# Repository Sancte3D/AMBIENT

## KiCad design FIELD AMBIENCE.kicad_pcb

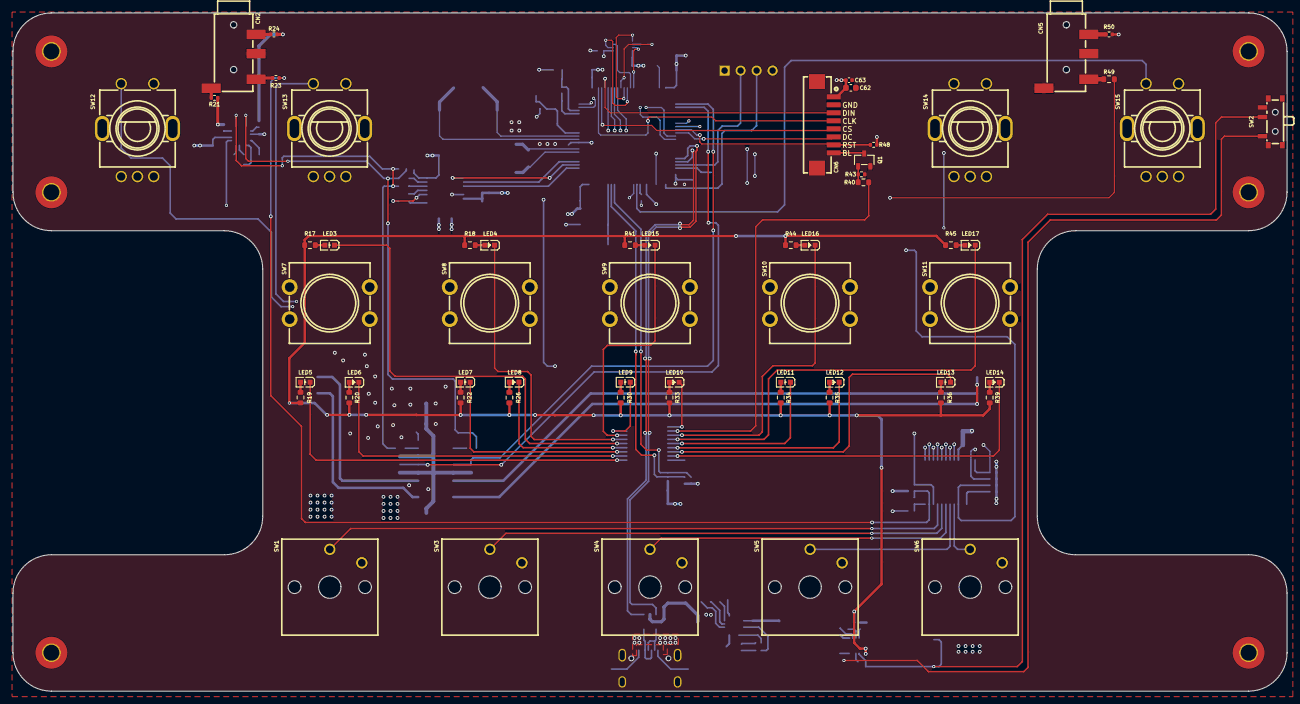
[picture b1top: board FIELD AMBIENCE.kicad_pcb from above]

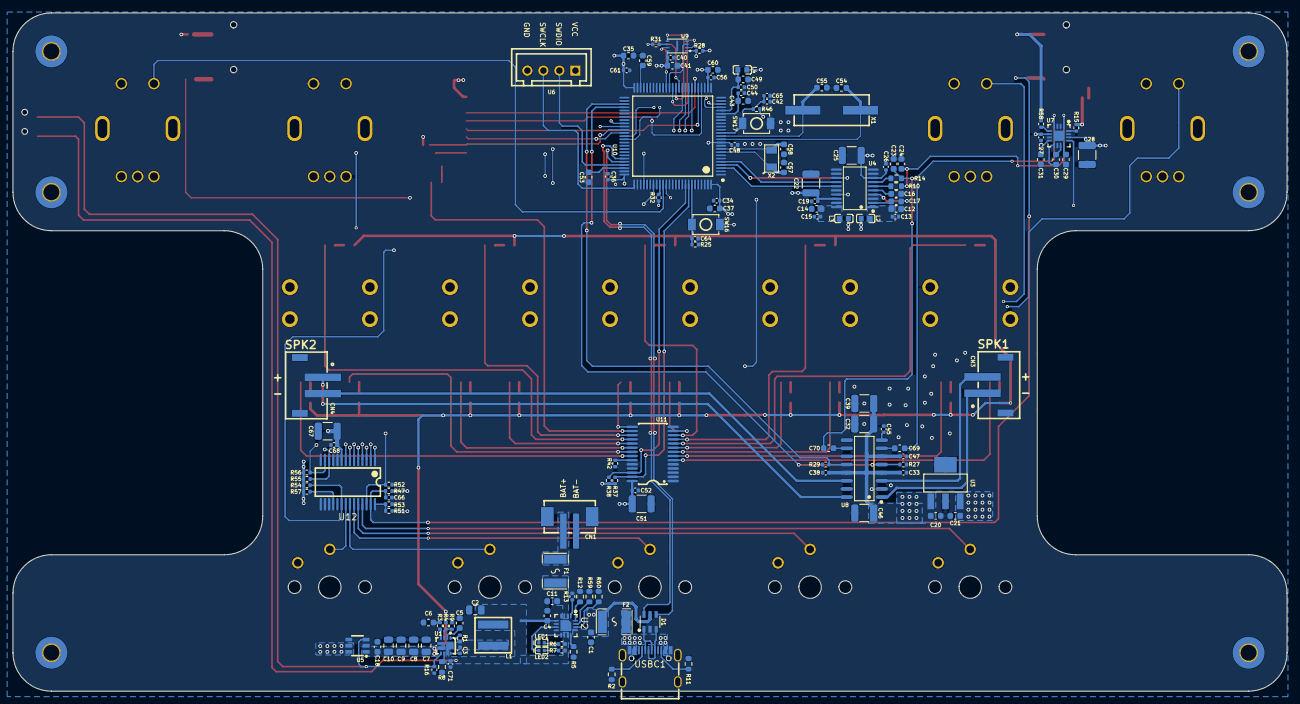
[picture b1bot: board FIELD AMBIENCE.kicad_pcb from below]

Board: 4 copper layers, 198.9 x 105.9 mm, 200 parts (135 on the bottom side), 159 nets.

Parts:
C1, C18, C30, C31, C69, C70: 1uF; C_0603_1608Metric
C2, C7, C8, C9, C10: 22uF; C_0805_2012Metric
C3, C13, C15, C19, C26, C27, C33, C34, C36, C38, C40, C42, C44, C45, C47, C48, C50, C52, C56, C61, C63, C64, C65, C66, C68, C71: 100nF; C_0402_1005Metric
C4, C11, C20, C21, C35, C62: 4.7uF; C_0603_1608Metric
C5, C16, C17, C23, C24, C29, C53, C59: 2.2uF; C_0603_1608Metric
C6: 4.7nF; C_0603_1608Metric
C12, C14, C37, C41, C43, C49, C60: 10uF; C_0603_1608Metric
C22, C25, C28, C32, C39, C46, C51, C67: 10uF; C_1210_3225Metric
C54, C55: 27pF; C_0603_1608Metric
C57, C58: 15pF; C_0603_1608Metric
CN1: B2B-PH-SM4-TBT; CONN-SMD_B2B-PH-SM4-TBT-LF-SN
CN2, CN5: PJ-320D; AUDIO-SMD_PJ-320D-1
CN3, CN4: 2.54-2P LT; CONN-SMD_2.54-2PLT
CN6: HC-1.25-8PWT; CONN-SMD_HC-1.25-8PWT
D1: USBLC6-2SC6; SOT-23-6_L2.9-W1.6-P0.95-LS2.8-BL
F1: 1812P260TF; F1812
F2: 1812L300/16GR; F1812
H2, H3, H4, H5, H6, H7: MountingHole_Pad; MountingHole_2.5mm_Pad_TopBottom
L1: 1.8uH; IND-SMD_L5.5-W5.3_YSPIT0530A
L2, L3: BLM18AG601SN1D; L0603
L4: BLM18PG121SN1D; L0603
LED1, LED2: YLED0402B; LED0402-RD
LED3, LED5, LED7, LED9, LED11, LED13: Yellow; LED0603-R-RD
LED4, LED6, LED8, LED10, LED12, LED14: Green; LED0603-RD
LED15, LED16, LED17: XL-1608UWC-04; LED0603-RD_WHITE
Q1: 2N7002_C916396; SOT-23-3_L2.9-W1.3-P1.90-LS2.4-BR
R1: 301K; R_0402_1005Metric
R2, R11: 5.1K; R_0603_1608Metric
R3: 17.4K; R_0402_1005Metric
R4: 332K; R_0402_1005Metric
R5: 1.1K; R_0603_1608Metric
R6, R7: 1.5K; R_0402_1005Metric
R8: 348K; R_0603_1608Metric
R9: 107K; R_0402_1005Metric
R10, R14: 470R; R_0603_1608Metric
R12: 887R; R_0603_1608Metric
R13, R23, R25, R28, R42, R43, R46, R47, R48, R50, R52, R54, R57: 10K; R_0402_1005Metric
R15, R58: 0R; R_0402_1005Metric
R16, R27, R29, R32, R51: 100K; R_0402_1005Metric
R17, R18, R19, R20, R22, R26, R30, R33, R34, R35, R36, R39, R41, R44, R45: 390R; R_0603_1608Metric
R21, R24, R31: 33R; R_0402_1005Metric
R37, R38, R55, R56: 4.7K; R_0402_1005Metric
R40: 100R; R_0603_1608Metric
R49: 220R; R_0603_1608Metric
R53: 200K; R_0402_1005Metric
R59: 590R; R_0603_1608Metric
R60: 37.4K; R_0603_1608Metric
SW1, SW3, SW4, SW5, SW6: CPG135001D01; KEY-TH_CPG135001D0X
SW2: SSSS811101; SW-SMD_SSSS811101
SW7, SW8, SW9, SW10, SW11: HX B3F-4055-Y; SW-TH_4P-L12.0-W12.0-P5.00-LS12.5_HX-B3F-4055-Y
SW12, SW13, SW14, SW15: EC11E18244AU; SW-TH_EC11XXXXXXXX
SW16, SW17: TS-1088; SW-SMD_L3.9-W3.0-P4.45
U1: TPS61089RNRR; VQFN-HR_L2.5-W2.0-P0.50-TL-EP
U2: BQ24074RGTR; QFN-16_L3.0-W3.0-P0.50-TL-EP1.7
U3: AP7361C-33E-13; SOT-223_L6.5-W3.5-P2.30-LS7.0-BR
U4: PCM5102APWR; TSSOP-20_L6.5-W4.4-P0.65-LS6.4-BL
U5: TPS22918DBVR; SOT-23-6_L2.9-W1.6-P0.95-LS2.8-BR
U6: B4B-XH-A; CONN-TH_B4B-XH-A-BK-LF-SN
U7: TPA6132A2RTER; WQFN-16_L3.0-W3.0-P0.50-TL-EP1.6
U8: PAM8403DR; SOIC-16_L9.9-W3.9-P1.27-LS6.0-BL
U9: APS6404L-3SQR-ZR; USON-8_L3.0-W2.0-P0.50-BL-EP
U10: STM32H743VIT6_C114409; LQFP-100_L14.0-W14.0-P0.50-LS16.0-BL
U11: PCA9685PW,118; TSSOP-28_L9.7-W4.4-P0.65-LS6.4-TL
U12: MCP23017T-E/SS; SSOP-28_L10.2-W5.3-P0.65-LS7.8-BL
USBC1: TYPE-C-31-M-12; USB-C_SMD-TYPE-C-31-M-12_1
X1: ABLS-8.000MHZ-B4-T; CRYSTAL-SMD_L11.4-W4.7-LS12.7
X2: ABS07-32.768KHZ-T; OSC-SMD_2P-L3.2-W1.5

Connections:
3.3V: C19.2, C21.2, C22.1, C25.2, C26.2, C27.2, C28.2, C34.2, C35.2, C36.1, C37.2, C40.2, C41.2, C48.2, C51.2, C52.2, C56.2, C60.2, C61.2, C62.2, C63.2, C67.2, C68.2, CN6.1, L2.1, L3.2, L4.2, R28.1, R37.1, R38.1, R46.1, R47.2, R48.1, R50.2, R54.1, R55.1, R56.1, R57.1, SW16.2, U3.3 (OUT), U4.8 (AVDD), U4.18 (LDOO), U6.1, U7.6 (G0), U7.14 (VDD), U9.8 (VDD), U10.11 (VDD), U10.27 (VDD), U10.50 (VDD), U10.75 (VDD), U10.100 (VDD), U11.28 (VDD), U12.9 (VDD)
+5V: C7.2, C8.2, C9.2, C10.2, C18.2, R4.1, R17.1, R18.1, R19.1, R20.1, R22.1, R26.1, R30.1, R33.1, R34.1, R35.1, R36.1, R39.1, R41.1, R44.1, R45.1, U1.6 (VOUT), U5.1 (VIN)
+5V_SW: C20.2, C32.2, C33.2, C38.2, C39.2, C46.2, C47.2, U3.1 (IN), U5.5 (QOD), U5.6 (VOUT), U8.4 (PVDD), U8.6 (VDD), U8.13 (PVDD)
+OUT_L: CN3.1, U8.1 (+OUT_L)
+OUT_R: CN4.1, U8.16 (+OUT_R)
-OUT_L: CN3.2, U8.3 (-OUT_L)
-OUT_R: CN4.2, U8.14 (-OUT_R)
BCK: U4.13 (BCK), U10.4 (PE5)
BOOT: C64.2, R25.2, SW16.1, U10.94 (BOOT0)
Backlight: CN6.8, Q1.3 (D)
CE: R28.2, U9.1 (/CE), U10.79 (PC11)
DIN: U4.14 (DIN), U10.5 (PE6)
DR+: D1.3 (I/O2), USBC1.A6 (DP1), USBC1.B6 (DP2)
DR-: D1.1 (I/O1), USBC1.A7 (DN1), USBC1.B7 (DN2)
Detect: C66.2, R23.1, R47.1, U12.27 (GPA6)
EXTI4: SW15.D, U10.85 (PD4)
FB: R4.2, R9.1, U1.3 (FB)
GND: C1.1, C2.1, C4.1, C5.1, C6.1, C7.1, C8.1, C9.1, C10.1, C11.2, C12.1, C13.1, C14.1, C15.1, C16.1, C18.1, C19.1, C20.1, C21.1, C22.2, C23.2, C24.2, C25.1, C26.1, C27.1, C28.1, C29.2, C31.1, C32.1, C33.1, C34.1, C35.1, C36.2, C37.1, C38.1, C39.1, C40.1, C41.1, C42.1, C43.1, C44.1, C45.1, C46.1, C47.1, C48.1, C49.1, C50.1, C51.1, C52.1, C53.2, C54.1, C55.1, C56.1, C57.1, C58.1, C59.2, C60.1, C61.1, C62.1, C63.1, C64.1, C65.1, C66.1, C67.1, C68.1, C71.2, CN1.2, CN2.3, CN5.1, CN6.2, D1.2 (GND), Q1.2 (S), R2.1, R5.1, R8.1, R9.2, R11.1, R12.1, R13.1, R16.1, R25.1, R27.1, R29.1, R42.2, R43.2, R52.2, R53.1, R59.1, R60.1, SW1.2, SW3.2, SW4.2, SW5.2, SW6.2, SW7.2, SW8.2, SW9.2, SW10.2, SW11.2, SW12.C, SW12.E, SW13.C, SW13.E, SW14.C, SW14.E, SW15.C, SW15.E, SW17.2, U1.5 (GND), U2.4 (CE#), U2.6 (EN1), U2.8 (VSS), U2.17 (EP), U3.2 (GND), U3.4 (GND), U4.3 (CPGND), U4.9 (AGND), U4.10 (DEMP), U4.11 (FLT), U4.12 (SCK), U4.16 (FMT), U4.19 (DGND), U5.2 (GND), U6.4, U7.2 (INL+), U7.3 (INR+), U7.7 (G1), U7.10 (PGND), U7.15 (SGND), U7.17 (EP), U8.2 (PGND), U8.11 (GND), U8.15 (PGND), U9.4 (VSS), U10.10 (VSS), U10.19 (VSSA), U10.26 (VSS), U10.49 (VSS), U10.74 (VSS), U10.99 (VSS), U11.1 (A0), U11.2 (A1), U11.3 (A2), U11.4 (A3), U11.5 (A4), U11.14 (VSS), U11.24 (A5), U12.10 (VSS), U12.15 (A0), U12.16 (A1), U12.17 (A2), USBC1.1 (EH), USBC1.2 (EH), USBC1.3 (EH), USBC1.4 (EH), USBC1.A1B12 (GND), USBC1.B1A12 (GND)
GPA0: SW6.1, U12.21 (GPA0)
GPA1: SW5.1, U12.22 (GPA1)
GPA2: SW4.1, U12.23 (GPA2)
GPA3: SW3.1, U12.24 (GPA3)
GPA5: SW1.1, U12.25 (GPA4)
GPA7: R51.1, R53.2, U12.28 (GPA7)
GPB0: SW7.3, U12.1 (GPB0)
GPB1: SW8.3, U12.2 (GPB1)
GPB2: SW9.3, U12.3 (GPB2)
GPB3: SW10.3, U12.4 (GPB3)
GPB4: SW11.3, U12.5 (GPB4)
GPB5: SW12.D, U12.6 (GPB5)
GPB6: SW13.D, U12.7 (GPB6)
GPB7: SW14.D, U12.8 (GPB7)
Interrupt: R54.2, U10.82 (PD1), U12.20 (INTA)
LCD CS: CN6.5, U10.30 (PA6)
LCD DC: CN6.6, U10.62 (PD15)
LCD RST: CN6.7, R48.2, U10.61 (PD14)
LCD SCK: CN6.4, U10.29 (PA5)
LD0: LED5.2 (K), U11.6 (LED0)
LD1: LED6.1 (K), U11.7 (LED1)
LD2: LED7.2 (K), U11.8 (LED2)
LD3: LED8.1 (K), U11.9 (LED3)
LD4: LED3.2 (K), U11.10 (LED4)
LD5: LED17.1 (K), U11.18 (LED11)
LD6: LED15.1 (K), U11.12 (LED6)
LD7: LED16.1 (K), U11.17 (LED10)
LD8: LED10.1 (K), U11.15 (LED8)
LD9: LED9.2 (K), U11.13 (LED7)
LD10: LED4.1 (K), U11.11 (LED5)
LD11: LED13.2 (K), U11.21 (LED14)
LD12: LED12.1 (K), U11.20 (LED13)
LD13: LED11.2 (K), U11.19 (LED12)
LD14: R40.1, U11.16 (LED9)
LD15: LED14.1 (K), U11.22 (LED15)
LRCK: U4.15 (LRCK), U10.3 (PE4)
MOSI: CN6.3, U10.31 (PA7)
MUTE: R27.2, U8.5 (MUTE), U10.54 (PB15)
NRST: C42.2, C65.2, R46.2, SW17.1, U10.14 (NRST)
unnamed: C6.2, R3.1
unnamed: C53.1, U10.73 (VCAP)
unnamed: C59.1, U10.48 (VCAP)
unnamed: CN1.1, F1.2
unnamed: CN2.1, R21.1
unnamed: CN2.2, R24.1
unnamed: CN2.4, R23.2
unnamed: CN5.2, R50.1
unnamed: CN5.4, R49.1
unnamed: LED1.2 (A), R6.1
unnamed: LED1.1 (K), U2.9 (CHG#)
unnamed: LED2.2 (A), R7.1
unnamed: LED2.1 (K), U2.7 (PGOOD#)
unnamed: LED3.1 (A), R17.2
unnamed: LED4.2 (A), R18.2
unnamed: LED5.1 (A), R19.2
unnamed: LED6.2 (A), R20.2
unnamed: LED7.1 (A), R22.2
unnamed: LED8.2 (A), R26.2
unnamed: LED9.1 (A), R30.2
unnamed: LED10.2 (A), R33.2
unnamed: LED11.1 (A), R34.2
unnamed: LED12.2 (A), R35.2
unnamed: LED13.1 (A), R36.2
unnamed: LED14.2 (A), R39.2
unnamed: LED15.2 (A), R41.2
unnamed: LED16.2 (A), R44.2
unnamed: LED17.2 (A), R45.2
unnamed: Q1.1 (G), R40.2, R43.1
unnamed: C3.1, U1.10 (BOOT)
unnamed: R3.2, U1.4 (COMP)
unnamed: R1.2, U1.1 (FSW)
unnamed: R8.2, U1.8 (ILIM)
unnamed: C3.2, L1.2, R1.1, U1.11 (SW)
unnamed: C5.2, U1.2 (VCC)
unnamed: R5.2, U2.12 (ILIM)
unnamed: R12.2, U2.16 (ISET)
unnamed: R59.2, U2.15 (ITERM)
unnamed: R60.2, U2.14 (TMR)
unnamed: R13.2, U2.1 (TS)
unnamed: C17.2, U4.4 (CAPM)
unnamed: C17.1, U4.2 (CAPP)
unnamed: C12.2, C13.2, L2.2, U4.1 (CPVDD)
unnamed: C14.2, C15.2, L3.1, U4.20 (DVDD)
unnamed: R10.2, U4.6 (OUTL)
unnamed: R14.2, U4.7 (OUTR)
unnamed: C16.2, U4.5 (VNEG)
unnamed: C30.1, U7.9 (CPN)
unnamed: C30.2, U7.11 (CPP)
unnamed: C29.1, U7.12 (HPVDD)
unnamed: C31.2, U7.8 (HPVSS)
unnamed: R15.1, U7.16 (OUTL)
unnamed: R58.2, U7.5 (OUTR)
unnamed: C69.1, U8.7 (INL)
unnamed: C70.1, U8.10 (INR)
unnamed: C45.2, U8.8 (VREF)
unnamed: R31.1, U9.6 (SCLK)
unnamed: R32.1, U10.84 (PD3)
unnamed: C49.2, C50.2, L4.1, U10.21 (VDDA)
unnamed: R42.1, U11.23 (OE#)
unnamed: R57.2, U12.18 (RESET#)
unnamed: R2.2, USBC1.A5 (CC1)
unnamed: R11.2, USBC1.B5 (CC2)
OSC32_IN: C57.2, U10.8 (PC14-OSC32_IN), X2.1 (OSC1)
OSC32_OUT: C58.2, U10.9 (PC15-OSC32_OUT), X2.2 (OSC2)
OSC_IN: C54.2, U10.12 (PH0-OSC_IN), X1.1 (OSC1)
OSC_OUT: C55.2, U10.13 (PH1-OSC_OUT), X1.2 (OSC2)
OUT DR+: D1.4 (I/O2), U10.71 (PA12)
OUT DR-: D1.6 (I/O1), U10.70 (PA11)
PA0: SW12.A, U10.22 (PA0)
PA1: SW12.B, U10.23 (PA1)
PB0: SW15.B, U10.35 (PB1)
PB1: SW15.A, U10.34 (PB0)
PC4: SW14.A, U10.32 (PC4)
PC5: SW14.B, U10.33 (PC5)
PC6: SW13.A, U10.64 (PC7)
PC7: SW13.B, U10.63 (PC6)
PWR_ON: R16.2, SW2.2, U1.7 (EN), U5.3 (ON)
R_LO_L: R15.2, R21.2
R_LO_R: R24.2, R58.1
R_VOL_L: C24.1, C69.2, R10.1, U7.1 (INL-)
R_VOL_R: C23.1, C70.2, R14.1, U7.4 (INR-)
SCL MCP: R55.2, U10.59 (PD12), U12.12 (SCK)
SCL PCA: R38.2, U10.92 (PB6), U11.26 (SCL)
SCLK: R31.2, U10.36 (PB2)
SDA MCP: R56.2, U10.60 (PD13), U12.13 (SDA)
SDA PCA: R37.2, U10.93 (PB7), U11.27 (SDA)
SHDN: R29.2, U8.12 (SHND), U10.53 (PB14)
SIO0: U9.5 (SI/SIO), U10.37 (PE7)
SIO1: U9.2 (SO/SIO), U10.38 (PE8)
SIO2: U9.3 (SIO), U10.39 (PE9)
SIO3: U9.7 (SIO), U10.40 (PE10)
SWCLKS: U6.3, U10.76 (PA14)
SWDIOS: U6.2, U10.72 (PA13)
TPA6132-EN: R32.2, U7.13 (EN)
USART2_TX: R49.2, U10.86 (PD5)
VBUS: C1.2, D1.5 (VBUS), F2.1, R51.2, U2.13 (IN)
VBUS0: F2.2, USBC1.A4B9 (VBUS), USBC1.B4A9 (VBUS)
VREF+: C43.2, C44.2, U10.20 (VREF+)
VSYS: C2.2, C4.2, C71.1, L1.1, R6.2, R7.2, SW2.1, U1.9 (VIN), U2.5 (EN2), U2.10 (OUT), U2.11 (OUT)
XSMT: R52.1, U4.17 (XSMT), U12.26 (GPA5)
battery: C11.1, F1.1, U2.2 (BAT), U2.3 (BAT)

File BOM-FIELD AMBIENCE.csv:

Comment,Designator,Footprint,LCSC,Quantity
0R,"R15,R58",R_0402_1005Metric,C226739,2
1.1K,R5,R_0603_1608Metric,C22764,1
1.5K,"R6,R7",R_0402_1005Metric,C25867,2
1.8uH,L1,IND-SMD_L5.5-W5.3_YSPIT0530A,C18199436,1
100K,"R16,R27,R29,R32,R51",R_0402_1005Metric,C25741,5
100R,R40,R_0603_1608Metric,C105588,1
100nF,C71,C_0402_1005Metric,C14663,1
100nF,"C13,C15,C19,C26,C27,C3,C33,C34,C36,C38,C40,C42,C44,C45,C47,C48,C50,C52,C56,C61,C63,C64,C65,C66,C68",C_0402_1005Metric,C307331,25
107K,R9,R_0402_1005Metric,C138070,1
10K,"R13,R23,R25,R28,R42,R43,R46,R47,R48,R50,R52,R54,R57",R_0402_1005Metric,C5121989,13
10uF,"C22,C25,C28,C32,C39,C46,C51,C67",C_1210_3225Metric,C39232,8
10uF,"C12,C14,C37,C41,C43,C49,C60",C_0603_1608Metric,C96446,7
15pF,"C57,C58",C_0603_1608Metric,C1644,2
17.4K,R3,R_0402_1005Metric,C2933077,1
1812L300/16GR,F2,F1812,C18198349,1
1812P260TF,F1,F1812,C20814,1
1uF,"C1,C18,C30,C31,C69,C70",C_0603_1608Metric,C29936,6
2.2uF,"C16,C17,C23,C24,C29,C5,C53,C59",C_0603_1608Metric,C23630,8
2.54-2P LT,"CN3,CN4",CONN-SMD_2.54-2PLT,C668621,2
200K,R53,R_0402_1005Metric,C25764,1
220R,R49,R_0603_1608Metric,C2907014,1
22uF,"C10,C2,C7,C8,C9",C_0805_2012Metric,C602037,5
27pF,"C54,C55",C_0603_1608Metric,C107045,2
2N7002_C916396,Q1,SOT-23-3_L2.9-W1.3-P1.90-LS2.4-BR,C916396,1
301K,R1,R_0402_1005Metric,C3917912,1
332K,R4,R_0402_1005Metric,C138005,1
33R,"R21,R24,R31",R_0402_1005Metric,C138002,3
348K,R8,R_0603_1608Metric,C23006,1
37.4K,R60,R_0603_1608Metric,C23033,1
390R,"R17,R18,R19,R20,R22,R26,R30,R33,R34,R35,R36,R39,R41,R44,R45",R_0603_1608Metric,C23151,15
4.7K,"R37,R38,R55,R56",R_0402_1005Metric,C99782,4
4.7nF,C6,C_0603_1608Metric,C106218,1
4.7uF,"C11,C20,C21,C35,C4,C62",C_0603_1608Metric,C389010,6
470R,"R10,R14",R_0603_1608Metric,C114622,2
5.1K,"R11,R2",R_0603_1608Metric,C2907044,2
590R,R59,R_0603_1608Metric,C49654223,1
887R,R12,R_0603_1608Metric,C93619,1
ABLS-8.000MHZ-B4-T,X1,CRYSTAL-SMD_L11.4-W4.7-LS12.7,C596838,1
ABS07-32.768KHZ-T,X2,OSC-SMD_2P-L3.2-W1.5,C130253,1
AP7361C-33E-13,U3,SOT-223_L6.5-W3.5-P2.30-LS7.0-BR,C500795,1
APS6404L-3SQR-ZR,U9,USON-8_L3.0-W2.0-P0.50-BL-EP,C3040877,1
B2B-PH-SM4-TBT,CN1,CONN-SMD_B2B-PH-SM4-TBT-LF-SN,C265003,1
B4B-XH-A,U6,CONN-TH_B4B-XH-A-BK-LF-SN,C566013,1
BLM18AG601SN1D,"L2,L3",L0603,C19330,2
BLM18PG121SN1D,L4,L0603,C14709,1
BQ24074RGTR,U2,QFN-16_L3.0-W3.0-P0.50-TL-EP1.7,C54313,1
CPG135001D01,"SW1,SW3,SW4,SW5,SW6",KEY-TH_CPG135001D0X,C400229,5
EC11E18244AU,"SW12,SW13,SW14,SW15",SW-TH_EC11XXXXXXXX,C202365,4
Green,"LED10,LED12,LED14,LED4,LED6,LED8",LED0603-RD,C12624,6
HC-1.25-8PWT,CN6,CONN-SMD_HC-1.25-8PWT,C2845385,1
HX B3F-4055-Y,"SW10,SW11,SW7,SW8,SW9",SW-TH_4P-L12.0-W12.0-P5.00-LS12.5_HX-B3F-4055-Y,C36498965,5
MCP23017T-E/SS,U12,SSOP-28_L10.2-W5.3-P0.65-LS7.8-BL,C558584,1
PAM8403DR,U8,SOIC-16_L9.9-W3.9-P1.27-LS6.0-BL,C17337,1
"PCA9685PW,118",U11,TSSOP-28_L9.7-W4.4-P0.65-LS6.4-TL,C2678753,1
PCM5102APWR,U4,TSSOP-20_L6.5-W4.4-P0.65-LS6.4-BL,C107671,1
PJ-320D,"CN2,CN5",AUDIO-SMD_PJ-320D-1,C431535,2
SSSS811101,SW2,SW-SMD_SSSS811101,C109335,1
STM32H743VIT6_C114409,U10,LQFP-100_L14.0-W14.0-P0.50-LS16.0-BL,C114409,1
TPA6132A2RTER,U7,WQFN-16_L3.0-W3.0-P0.50-TL-EP1.6,C69901,1
TPS22918DBVR,U5,SOT-23-6_L2.9-W1.6-P0.95-LS2.8-BR,C131941,1
TPS61089RNRR,U1,VQFN-HR_L2.5-W2.0-P0.50-TL-EP,C165129,1
TS-1088,"SW16,SW17",SW-SMD_L3.9-W3.0-P4.45,C720477,2
TYPE-C-31-M-12,USBC1,USB-C_SMD-TYPE-C-31-M-12_1,C165948,1
USBLC6-2SC6,D1,SOT-23-6_L2.9-W1.6-P0.95-LS2.8-BL,C7519,1
XL-1608UWC-04,LED17,LED0603-RD_WHITE,C965800,1
XL-1608UWC-04,"LED15,LED16",LED0603-RD_WHITE,C965808,2
YLED0402B,"LED1,LED2",LED0402-RD,C30584803,2
Yellow,"LED11,LED13,LED3,LED5,LED7,LED9",LED0603-R-RD,C2287,6

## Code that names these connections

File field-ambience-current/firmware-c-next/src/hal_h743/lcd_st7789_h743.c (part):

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 * Step 13.3 — real driver; same lcd_st7789.h contract as the Pico driver).
 *
 * Pin map (DS12110 + generator NETS, r18.83-verified):
 *   PA5 (pin 29) = SPI1_SCK   (AF5) → LCD SCK
 *   PA7 (pin 31) = SPI1_MOSI  (AF5) → LCD MOSI (SDA)
 *   PA6 (pin 30) = GPIO out   → LCD CS   (idle HIGH)
 *   PC4 (pin 32) = GPIO out   → LCD DC   (data/command)
 *   PC5 (pin 33) = GPIO out   → LCD RES  (idle HIGH)
 *   Backlight    = PCA9685 ch15 (LCD_BLK_PWM gates Q2 2N7002) — set over
 *                  I²C in the board layer, not here (mirrors the Pico split).
 *
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    g.Mode  = GPIO_MODE_OUTPUT_PP;
    g.Pull  = GPIO_NOPULL;
    g.Speed = GPIO_SPEED_FREQ_LOW;
    g.Pin   = GPIO_PIN_6;                                    /* PA6 CS  */
    HAL_GPIO_Init(GPIOA, &g);
    g.Pin   = GPIO_PIN_4 | GPIO_PIN_5;                       /* PC4/PC5 */
    HAL_GPIO_Init(GPIOC, &g);

    /* SPI1: master TX-only, mode 0, MSB first, 8 bit, 120 MHz/4 = 30 MHz. */
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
